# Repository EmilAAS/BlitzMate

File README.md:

# BlitzMate
This repository contains files regarding, BlitzMate, a self playing chessboard tailored towards blitz chess. The project is the basis for my masters thesis in mechanical engineering

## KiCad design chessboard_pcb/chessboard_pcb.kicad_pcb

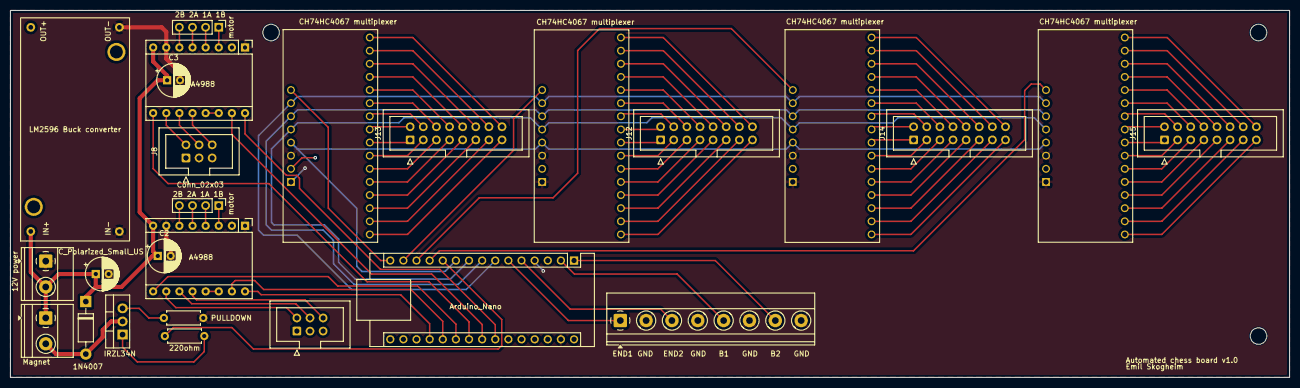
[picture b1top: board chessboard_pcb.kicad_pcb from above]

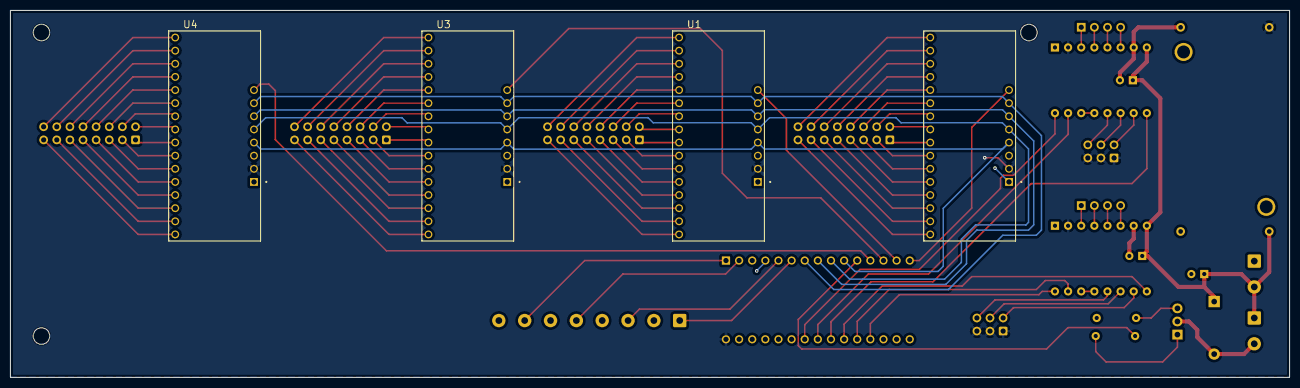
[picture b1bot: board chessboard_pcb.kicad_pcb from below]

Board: 2 copper layers, 247.5 x 71.0 mm, 29 parts (4 on the bottom side), 105 nets.

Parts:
A1: Arduino_Nano
A3, A4988 : A4988; Pololu_Breakout-16_15.2x20.3mm
BUCK1: LM2596
C1, C2, C3: C_Polarized_Small_US; CP_Radial_D6.3mm_P2.50mm
D1: 1N4007; D_DO-41_SOD81_P10.16mm_Horizontal
H1, H2, H3: MountingHole; MountingHole_3.2mm_M3
J1: screw_terminal_electromagnet; TerminalBlock_Phoenix_MKDS-1,5-2_1x02_P5.00mm_Horizontal
J2: screw_terminal_12volt_in; TerminalBlock_Phoenix_MKDS-1,5-2_1x02_P5.00mm_Horizontal
J7, J8: Conn_02x03; IDC-Header_2x03_P2.54mm_Vertical
J11: Screw_01x08; TerminalBlock_Phoenix_MKDS-1,5-8_1x08_P5.00mm_Horizontal
J12, J13, J14, J15: Conn_02x08; IDC-Header_2x08_P2.54mm_Vertical
PULLDOWN: 10K; R_Axial_DIN0207_L6.3mm_D2.5mm_P7.62mm_Horizontal
Q1: IRLZ34N; TO-220-3_Vertical
R1: 220; R_Axial_DIN0207_L6.3mm_D2.5mm_P7.62mm_Horizontal
U1, U3, U4: CD74HC4067M; multiplexer_module
motor: Conn_01x04; PinHeader_1x04_P2.54mm_Vertical
motor#2: Conn01x04; PinHeader_1x04_P2.54mm_Vertical
multiplexer: CD74HC4067M; multiplexer_module

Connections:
+5V: A1.30 (VIN), A3.2 (VDD), A4988.2 (VDD), BUCK1.3 (OUT+), J7.1, J7.3 (Pin_2), J7.5 (Pin_3), J8.1, J8.3 (Pin_2), J8.5 (Pin_3), U1.24 (VCC), U3.24 (VCC), U4.24 (VCC), multiplexer.24 (VCC)
+12V: A3.8 (VMOT), A4988.8 (VMOT), BUCK1.1 (IN+), C1.1, C2.1, C3.1, D1.1 (K), J1.1, J2.2
BUTTON1: A1.2 (D0/RX), J11.5
BUTTON2: A1.1 (D1/TX), J11.7
COM1: A1.14 (D11), U1.1 (COM)
COM2: A1.15 (D12), multiplexer.1 (COM)
COM3: A1.13 (D10), U3.1 (COM)
COM4: A1.12 (D9), U4.1 (COM)
DIR1: A1.24 (A5), A3.16 (DIR)
DIR2: A1.19 (A0), A4988.16 (DIR)
EN1: A1.22 (A3), A3.9 (~ENABLE)
EN2: A1.21 (A2), A4988.9 (~ENABLE)
ENDSTOP1: A1.6 (D3), J11.1
ENDSTOP2: A1.5 (D2), J11.3
GND: A1.4 (GND), A1.29 (GND), A3.1 (GND), A3.7 (GND), A4988.1 (GND), A4988.7 (GND), BUCK1.2 (IN-), BUCK1.4 (OUT-), C1.2, C2.2, C3.2, J2.1, J11.2, J11.4, J11.6, J11.8, PULLDOWN.1, U1.12 (GND), U1.15 (~E), U3.12 (GND), U3.15 (~E), U4.12 (GND), U4.15 (~E), multiplexer.12 (GND), multiplexer.15 (~E)
unnamed: A4988.4 (1A), motor#2.2 (Pin_3)
unnamed: A4988.3 (1B), motor#2.1 (Pin_4)
unnamed: A4988.5 (2A), motor#2.3 (Pin_2)
unnamed: A4988.6 (2B), motor#2.4 (Pin_1)
unnamed: A4988.10 (MS1), J7.2 (Pin_6)
unnamed: A4988.11 (MS2), J7.4 (Pin_5)
unnamed: A4988.12 (MS3), J7.6 (Pin_4)
unnamed: A4988.13 (~RESET), A4988.14 (~SLEEP)
unnamed: A3.4 (1A), motor.2 (Pin_3)
unnamed: A3.3 (1B), motor.1 (Pin_4)
unnamed: A3.5 (2A), motor.3 (Pin_2)
unnamed: A3.6 (2B), motor.4 (Pin_1)
unnamed: A3.10 (MS1), J8.2 (Pin_6)
unnamed: A3.11 (MS2), J8.4 (Pin_5)
unnamed: A3.12 (MS3), J8.6 (Pin_4)
unnamed: A3.13 (~RESET), A3.14 (~SLEEP)
unnamed: D1.2 (A), J1.2, Q1.2 (D)
unnamed: J12.10 (6), U1.6 (I3)
unnamed: J12.1, U1.23 (I8)
unnamed: J12.2, U1.2 (I7)
unnamed: J12.3, U1.22 (I9)
unnamed: J12.4, U1.3 (I6)
unnamed: J12.5, U1.21 (I10)
unnamed: J12.6, U1.4 (I5)
unnamed: J12.7, U1.20 (I11)
unnamed: J12.8, U1.5 (I4)
unnamed: J12.9, U1.19 (I12)
unnamed: J12.11, U1.18 (I13)
unnamed: J12.12, U1.7 (I2)
unnamed: J12.13, U1.17 (I14)
unnamed: J12.14, U1.8 (I1)
unnamed: J12.15, U1.16 (I15)
unnamed: J12.16, U1.9 (I0)
unnamed: J13.10 (6), multiplexer.6 (I3)
unnamed: J13.1, multiplexer.23 (I8)
unnamed: J13.2, multiplexer.2 (I7)
unnamed: J13.3, multiplexer.22 (I9)
unnamed: J13.4, multiplexer.3 (I6)
unnamed: J13.5, multiplexer.21 (I10)
unnamed: J13.6, multiplexer.4 (I5)
unnamed: J13.7, multiplexer.20 (I11)
unnamed: J13.8, multiplexer.5 (I4)
unnamed: J13.9, multiplexer.19 (I12)
unnamed: J13.11, multiplexer.18 (I13)
unnamed: J13.12, multiplexer.7 (I2)
unnamed: J13.13, multiplexer.17 (I14)
unnamed: J13.14, multiplexer.8 (I1)
unnamed: J13.15, multiplexer.16 (I15)
unnamed: J13.16, multiplexer.9 (I0)
unnamed: J14.10 (6), U3.6 (I3)
unnamed: J14.1, U3.23 (I8)
unnamed: J14.2, U3.2 (I7)
unnamed: J14.3, U3.22 (I9)
unnamed: J14.4, U3.3 (I6)
unnamed: J14.5, U3.21 (I10)
unnamed: J14.6, U3.4 (I5)
unnamed: J14.7, U3.20 (I11)
unnamed: J14.8, U3.5 (I4)
unnamed: J14.9, U3.19 (I12)
unnamed: J14.11, U3.18 (I13)
unnamed: J14.12, U3.7 (I2)
unnamed: J14.13, U3.17 (I14)
unnamed: J14.14, U3.8 (I1)
unnamed: J14.15, U3.16 (I15)
unnamed: J14.16, U3.9 (I0)
unnamed: J15.10 (6), U4.6 (I3)
unnamed: J15.1, U4.23 (I8)
unnamed: J15.2, U4.2 (I7)
unnamed: J15.3, U4.22 (I9)
unnamed: J15.4, U4.3 (I6)
unnamed: J15.5, U4.21 (I10)
unnamed: J15.6, U4.4 (I5)
unnamed: J15.7, U4.20 (I11)
unnamed: J15.8, U4.5 (I4)
unnamed: J15.9, U4.19 (I12)
unnamed: J15.11, U4.18 (I13)
unnamed: J15.12, U4.7 (I2)
unnamed: J15.13, U4.17 (I14)
unnamed: J15.14, U4.8 (I1)
unnamed: J15.15, U4.16 (I15)
unnamed: J15.16, U4.9 (I0)
unnamed: Q1.1 (G), R1.2
unnamed: PULLDOWN.2, Q1.3 (S)
S0: A1.7 (D4), U1.10 (S0), U3.10 (S0), U4.10 (S0), multiplexer.10 (S0)
S1: A1.8 (D5), U1.11 (S1), U3.11 (S1), U4.11 (S1), multiplexer.11 (S1)
S2: A1.9 (D6), U1.14 (S2), U3.14 (S2), U4.14 (S2), multiplexer.14 (S2)
S3: A1.10 (D7), U1.13 (S3), U3.13 (S3), U4.13 (S3), multiplexer.13 (S3)
STEP1: A1.23 (A4), A3.15 (STEP)
STEP2: A1.20 (A1), A4988.15 (STEP)
mag: A1.11 (D8), R1.1
